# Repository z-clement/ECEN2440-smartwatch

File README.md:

# ECEN2440-smartwatch

The final project for ECEN2440 Embedded Systems. Our group decided to make a smartwatch that has a touchscreen display
with the capabilities to set an alarm and timer using bluetooth.

The project uses an MSP432 as the microcontroller which communicates via UART with the display and bluetooth module.

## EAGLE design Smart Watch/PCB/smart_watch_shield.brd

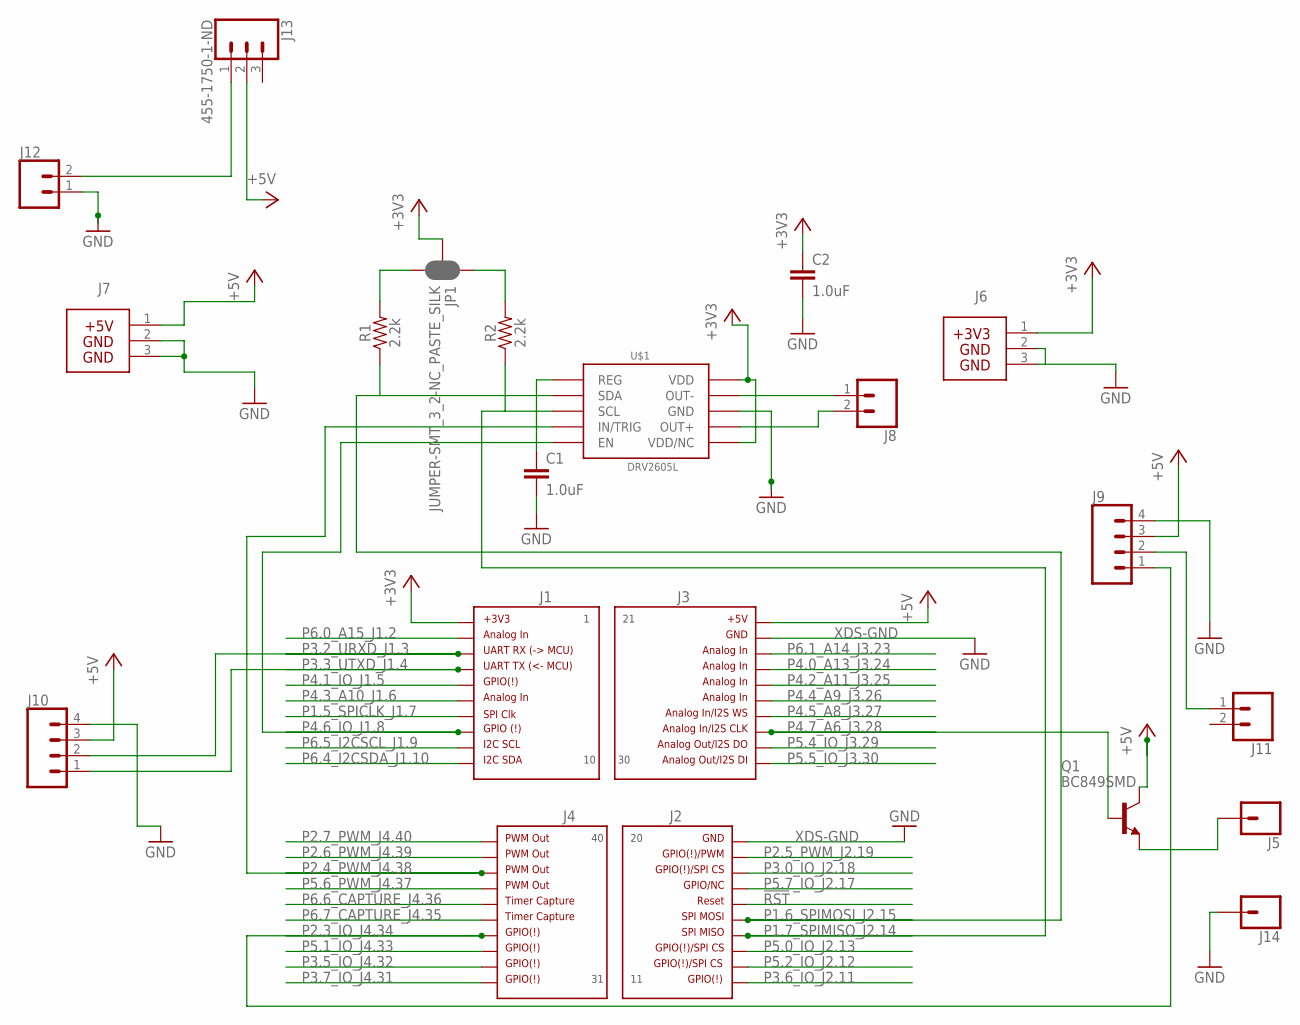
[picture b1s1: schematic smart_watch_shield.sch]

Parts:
C1, C2: 1.0uF; 0805
J1: HEADER1X10-J1SILK_LABELS; J1
J2: HEADER1X10-J2SILK_LABELS; J2
J3: HEADER1X10-J3; J3
J4: HEADER1X10-J4SILK_LABELS; J4
J5, J14: CONN_01; 1X01
J6: HEADER 1X03; 3PIN_PWR_3V3
J7: BP_HEADERS_PWR_5V; 3PIN_PWR_5V
J8, J11, J12: CONN_02; 1X02
J9, J10: CONN_04PTH; 1X04
J13: 455-1750-1-ND; 1X03
JP1: JUMPER-SMT_3_2-NC_PASTE_SILK; SMT-JUMPER_3_2-NC_PASTE_SILK
Q1: BC849SMD; SOT23-BEC
R1, R2: 2.2k; 0603
U$1: DRV2605L; VSSOP-10

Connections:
!RST: J2.16
+3V3: C2.1, J1.1, J6.1, JP1.2, U$1.P$6 (VDD/NC), U$1.P$10 (VDD)
+5V: J3.21, J7.1, J9.3, J10.3, J13.2, Q1.C
GND: C1.2, C2.2, J6.2, J6.3, J7.2, J7.3, J9.4, J10.4, J12.1, J14.1, U$1.P$8 (GND)
unnamed: JP1.3, R1.2
unnamed: JP1.1, R2.2
unnamed: J8.1, U$1.P$9 (OUT-)
unnamed: J9.2, J11.1
unnamed: J12.2, J13.1
unnamed: J5.1, Q1.E
unnamed: C1.1, U$1.P$1 (REG)
unnamed: J8.2, U$1.P$7 (OUT+)
P1.5_SPICLK_J1.7: J1.7
P1.6_SPIMOSI_J2.15: J2.15, R1.1, U$1.P$3 (SDA)
P1.7_SPIMISO_J2.14: J2.14, R2.1, U$1.P$2 (SCL)
P2.3_IO_J4.34: J4.34, J9.1
P2.4_PWM_J4.38: J4.38, U$1.P$4 (IN/TRIG)
P2.5_PWM_J2.19: J2.19
P2.6_PWM_J4.39: J4.39
P2.7_PWM_J4.40: J4.40
P3.0_IO_J2.18: J2.18
P3.2_URXD_J1.3: J1.3, J10.2
P3.3_UTXD_J1.4: J1.4, J10.1
P3.5_IO_J4.32: J4.32
P3.6_IO_J2.11: J2.11
P3.7_IO_J4.31: J4.31
P4.0_A13_J3.24: J3.24
P4.1_IO_J1.5: J1.5
P4.2_A11_J3.25: J3.25
P4.3_A10_J1.6: J1.6
P4.4_A9_J3.26: J3.26
P4.5_A8_J3.27: J3.27
P4.6_IO_J1.8: J1.8, U$1.P$5 (EN)
P4.7_A6_J3.28: J3.28, Q1.B
P5.0_IO_J2.13: J2.13
P5.1_IO_J4.33: J4.33
P5.2_IO_J2.12: J2.12
P5.4_IO_J3.29: J3.29
P5.5_IO_J3.30: J3.30
P5.6_PWM_J4.37: J4.37
P5.7_IO_J2.17: J2.17
P6.0_A15_J1.2: J1.2
P6.1_A14_J3.23: J3.23
P6.4_I2CSDA_J1.10: J1.10
P6.5_I2CSCL_J1.9: J1.9
P6.6_CAPTURE_J4.36: J4.36
P6.7_CAPTURE_J4.35: J4.35
XDS-GND: J2.20, J3.22

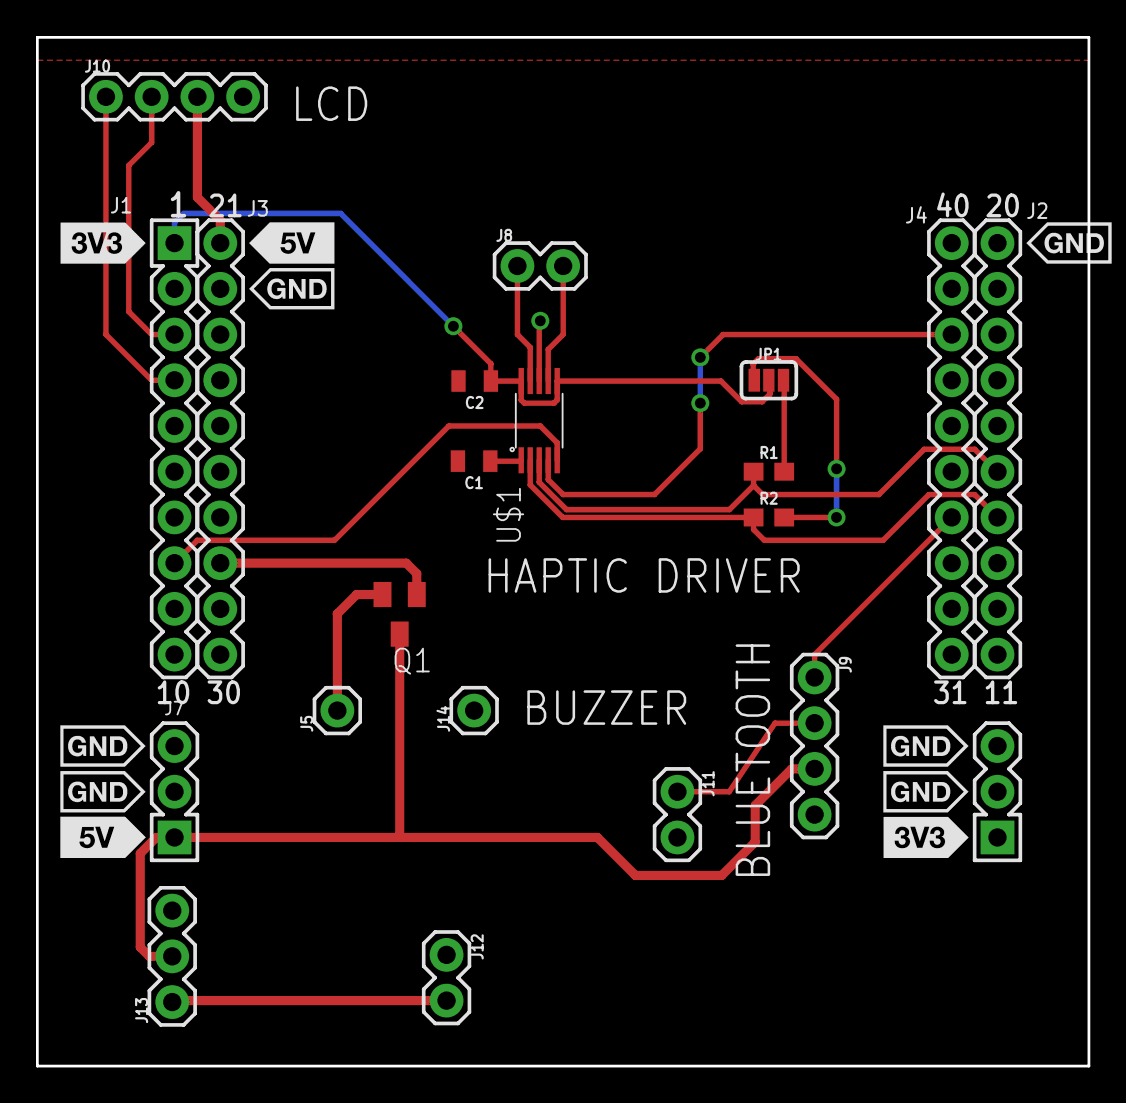
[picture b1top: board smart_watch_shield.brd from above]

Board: 2 copper layers, 58.4 x 57.1 mm, 21 parts (1 on the bottom side), 20 nets.

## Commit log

2019-11-27 Working circular buffer & parameterized uart
2019-11-27 Fixed errors with EUSCI as a parameter
2019-11-28 Updated example with screenRefresh.c allowing for uart comunication using both EUSCI_A1 and EUSCI_A2.
2019-11-28 Updated screen testing string to have termination characters on both sides of message. Also begining to implimnet the RTC fuctionality with uart functionality.
2019-11-29 In clock.c looking at the registers while debugging, everything seems to be working, however the minuete interupt flag gets set, but nothing happens. Will continue to search for the error tomorrow.
2019-11-30 Non working code
    In the debugger the value of MINUTEFLAG changes, however in the while
    loop the value of MINUTEFLAG is never not 1. When running the debugger
    the value of MINUTE flag goes to 1 but then it does not call the
    clockUpdate function. Not sure why this is happening. Also in the debug
    the stack pointer gets lost at certain points and the onboard LEDs do
    not light up.
2019-11-30 Changed around uart interrupt setup, implemented alarm and timer on rtc
2019-12-02 # WARNING: head commit changed in the meantime
    Fixed clock update issues. Added clock update functions.
2019-12-04 updated bluetooth to use utf-8 input instead of hex
2019-12-04 fixed comments
2019-12-04 Updated the screen refresh and added day of week display. And added alarmButton.c
2019-12-04 Working integration of the code version 1
2019-12-05 Added in DRV, PWM, and GPIO code for buzzer & DRV
2019-12-05 Working alarm button
2019-12-06 Working modular version.
2019-12-08 Added month and year display values. Also added changeAllTime function.
2019-12-09 Fixed bug where haptic driver wouldn't shut off.
2019-12-09 Reset so the alarm will start in the off position.
2019-12-09 Updated alarm enables to work
2019-12-11 Cleaned up code and added more comments
2019-12-17 Added datasheets
2019-12-17 Created folder for PCB files

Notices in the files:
parts and their libraries:
SparkFun-Connectors: Licensing: Creative Commons ShareAlike 4.0 International - https://creativecommons.org/licenses/by-sa/4.0
